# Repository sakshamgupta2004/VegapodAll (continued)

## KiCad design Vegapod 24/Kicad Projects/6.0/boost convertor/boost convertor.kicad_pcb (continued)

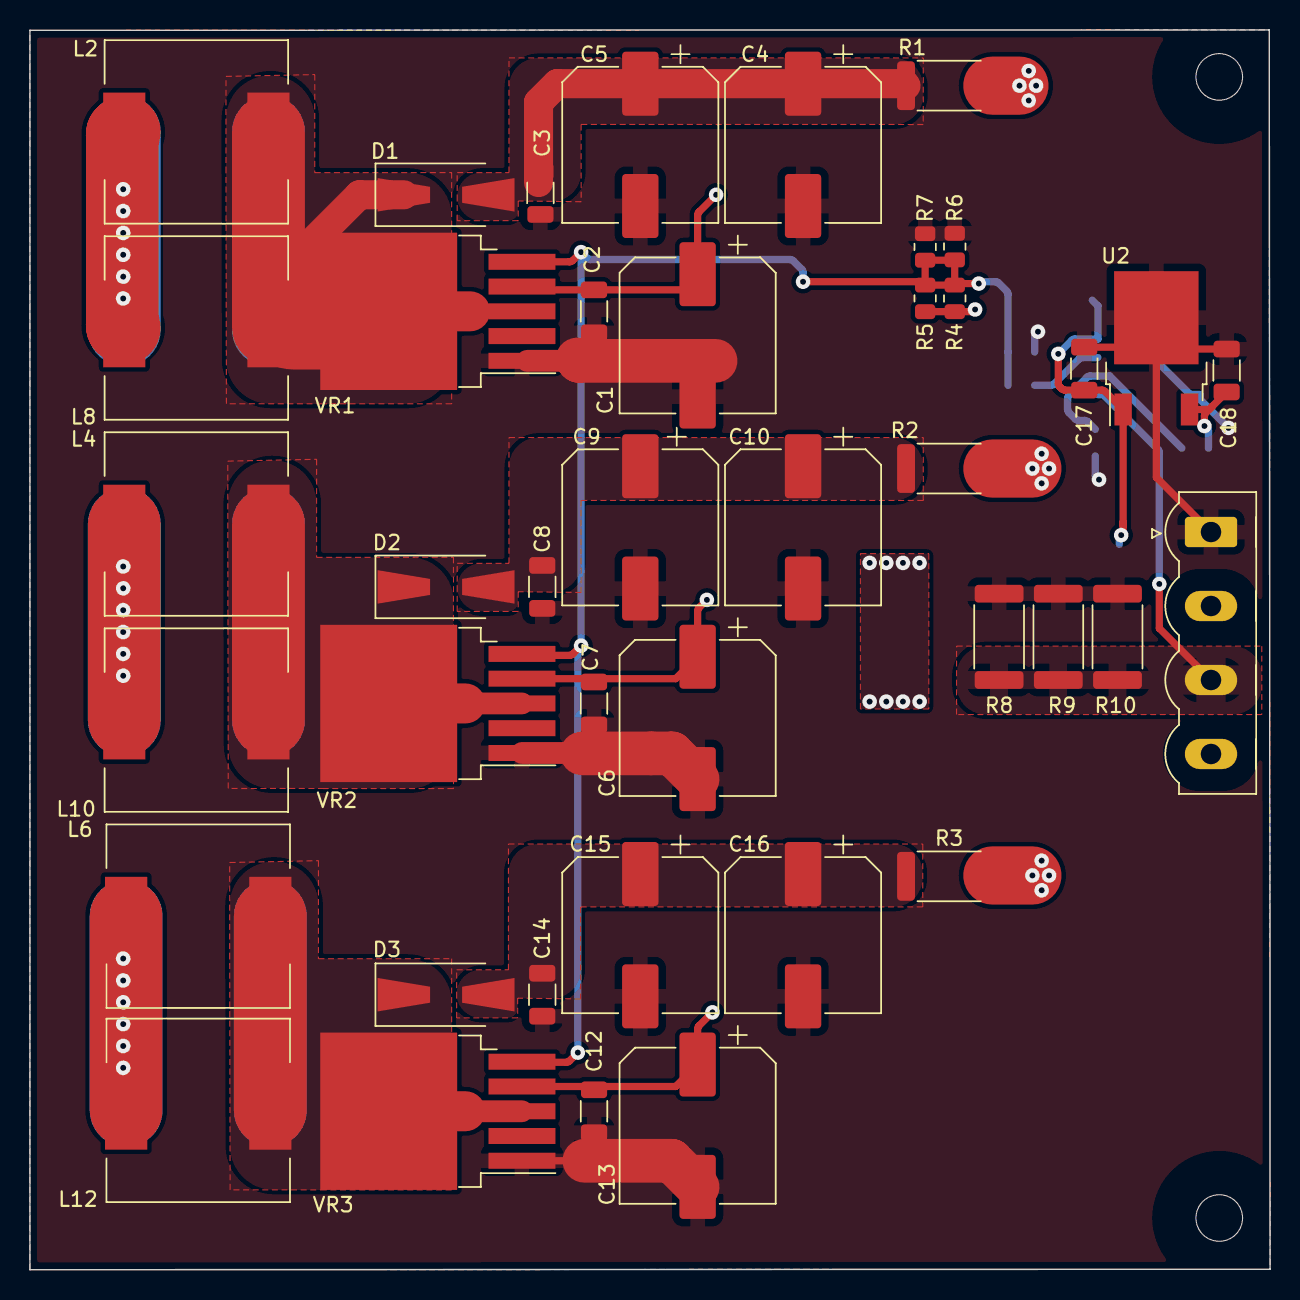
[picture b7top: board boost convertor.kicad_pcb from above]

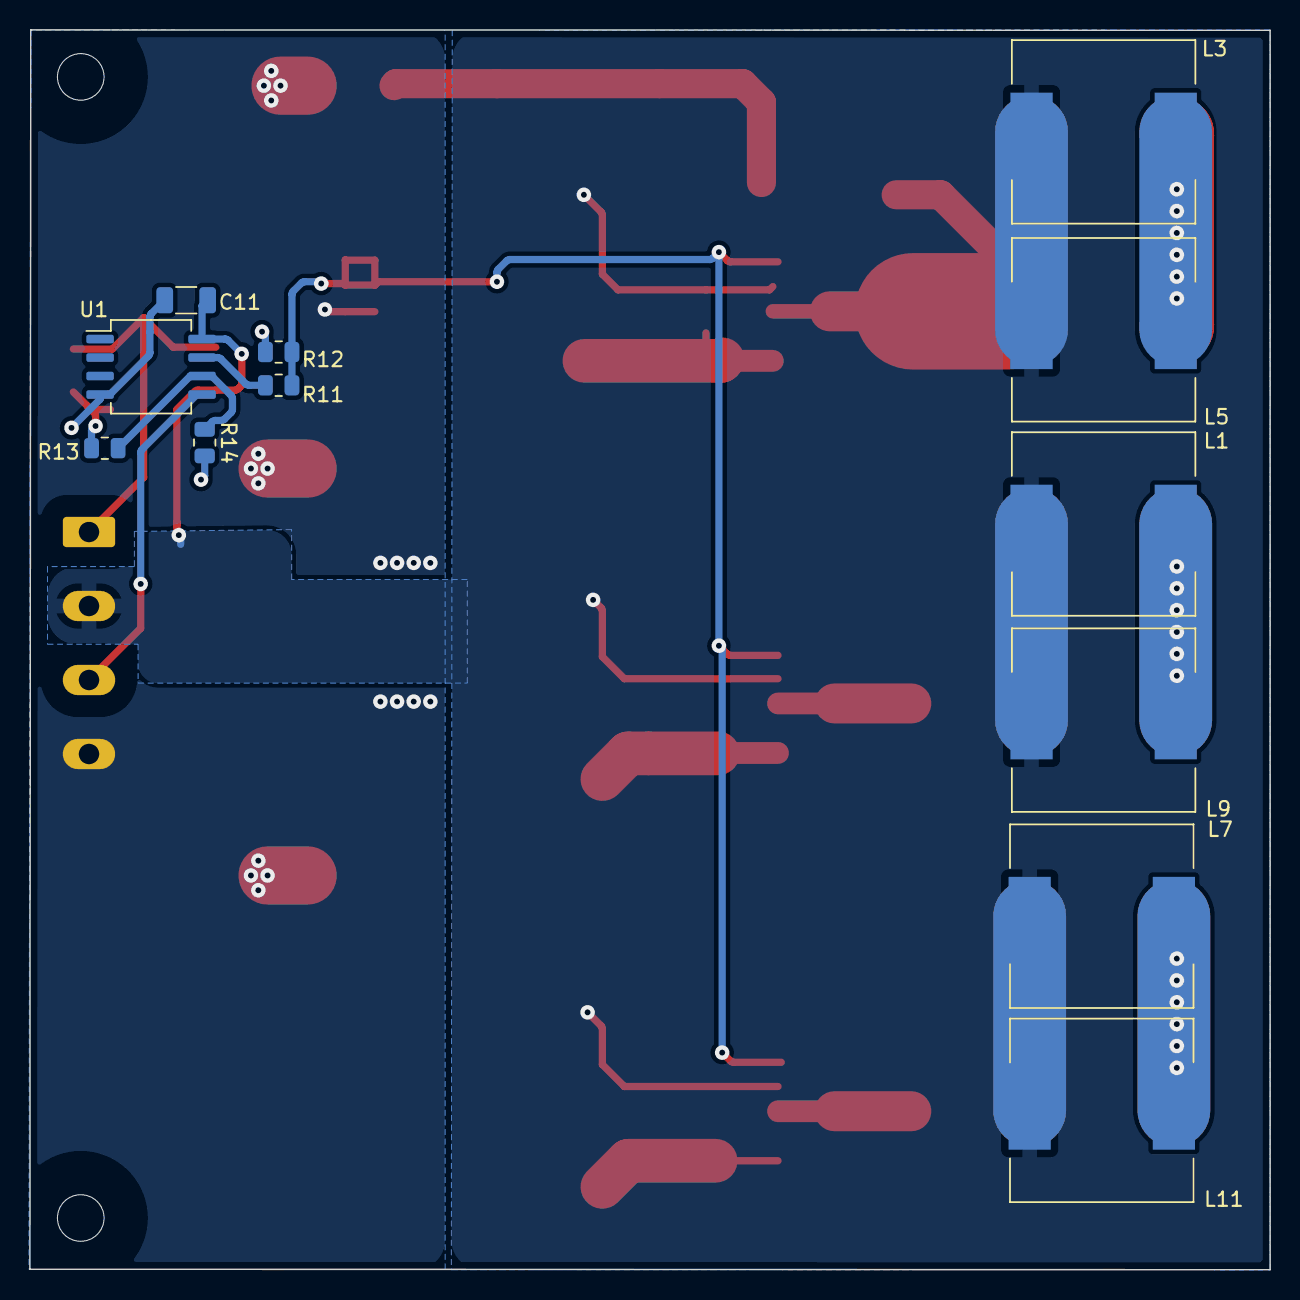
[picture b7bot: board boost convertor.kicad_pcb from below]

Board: 2 copper layers, 85.2 x 85.1 mm, 55 parts (12 on the bottom side), 17 nets.

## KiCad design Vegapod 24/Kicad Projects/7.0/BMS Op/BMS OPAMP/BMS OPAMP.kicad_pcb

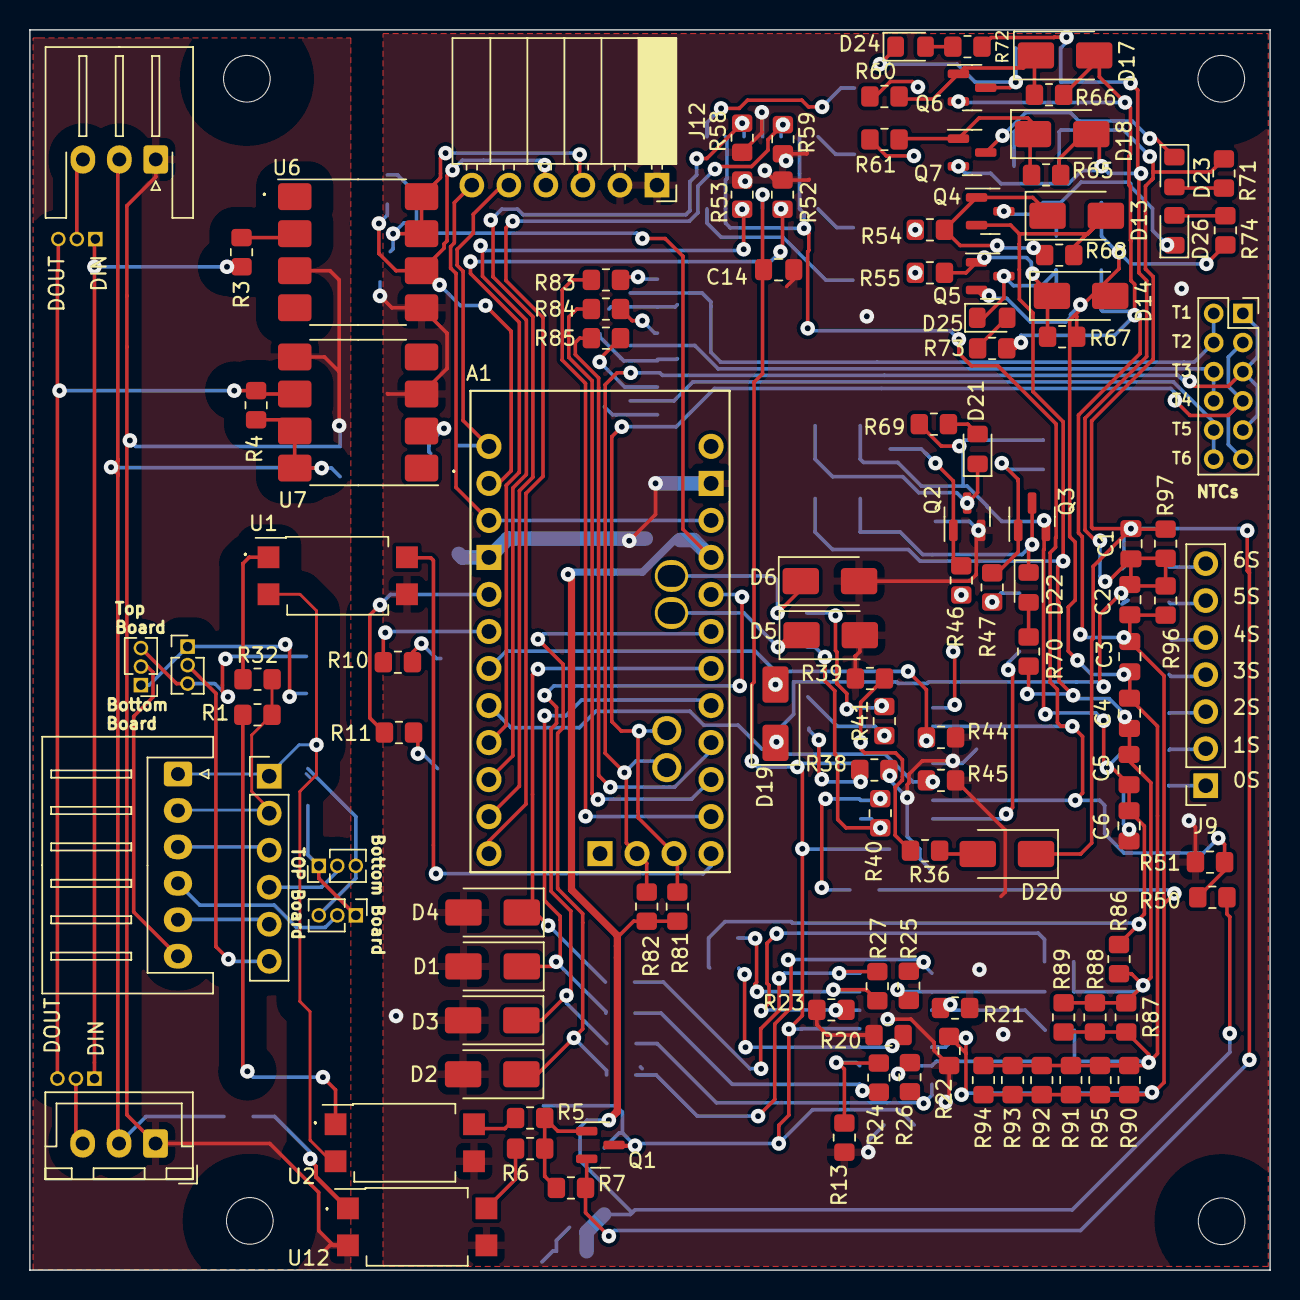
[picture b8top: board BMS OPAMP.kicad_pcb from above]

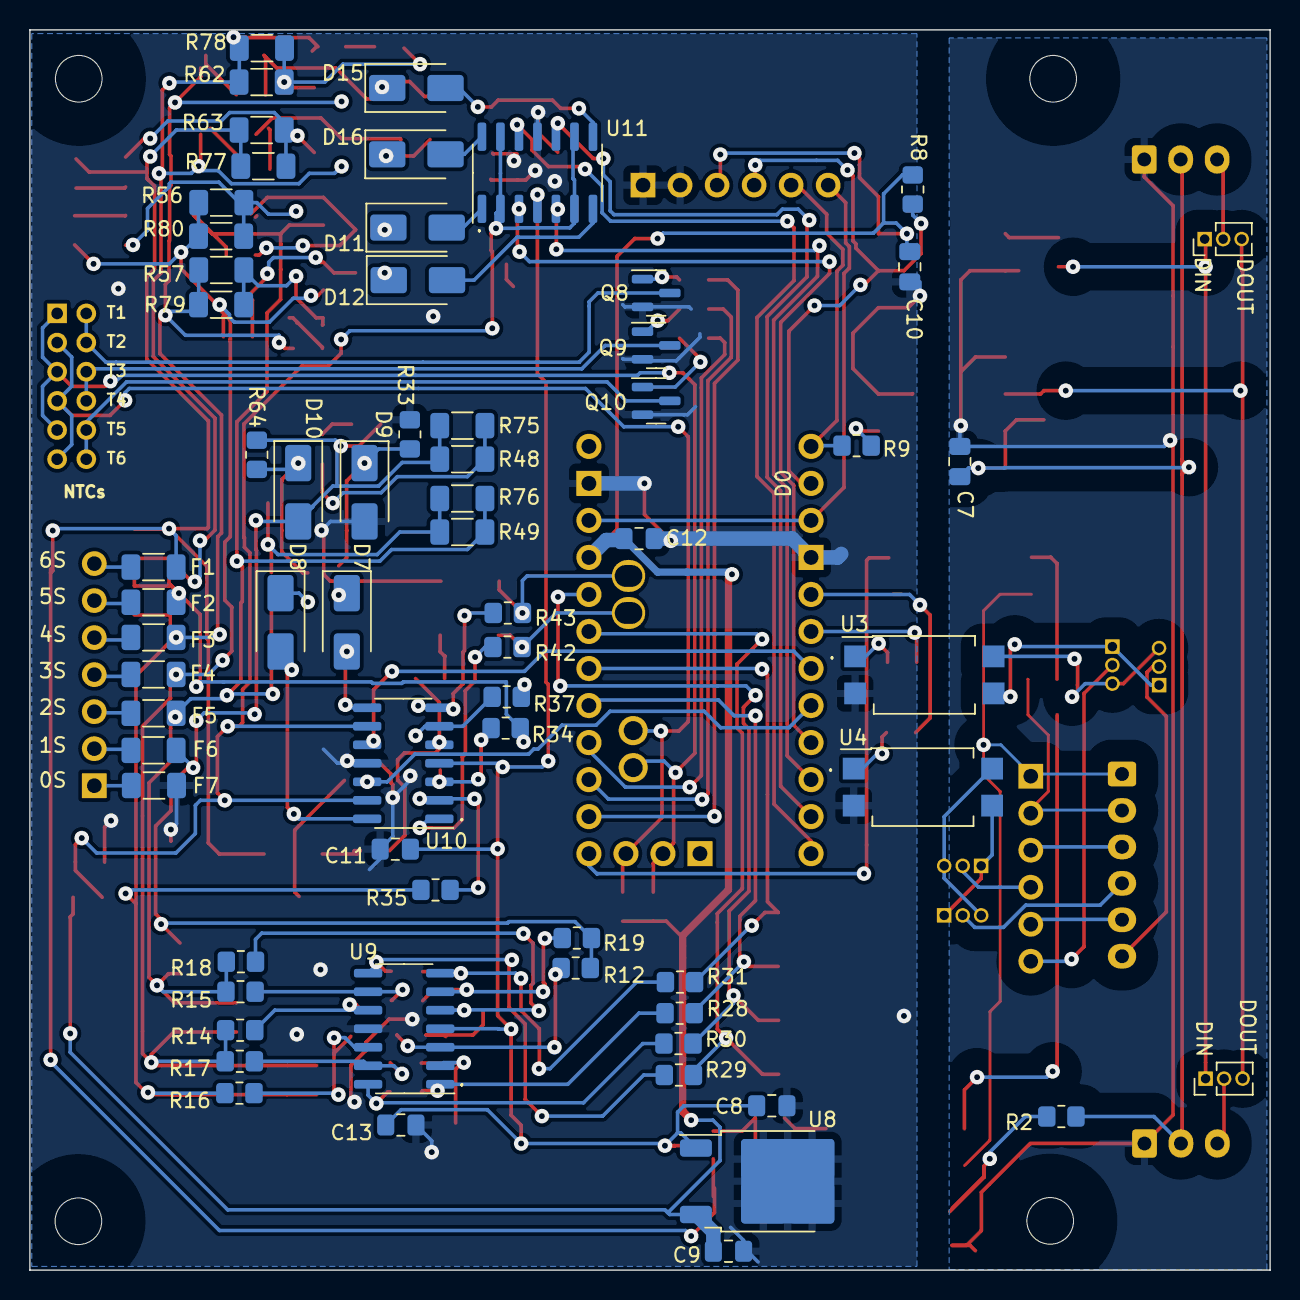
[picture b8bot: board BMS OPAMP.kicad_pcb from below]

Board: 2 copper layers, 85.1 x 85.1 mm, 183 parts (68 on the bottom side), 124 nets.

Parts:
A1: Clone_Pro_Mini_Socket_NoSPH
C1, C2, C3, C4, C5, C6, C7, C8, C9, C10, C11, C12, C13, C14: 1uF 25V; C_0805_2012Metric_Pad1.18x1.45mm_HandSolder
D1, D2, D3, D4, D5, D6: 5.1V Z; D_SMA
D7, D8, D11, D12, D15, D16: M7; D_SMA
D9, D10, D13, D14, D17, D18: 5V Z; D_SMA
D19, D20: Short It Out; D_SMA
D21, D22, D23, D24, D25, D26: LED; D_0805_2012Metric_Pad1.15x1.40mm_HandSolder
F1, F2, F3, F4, F5, F6, F7: Polyfuse_Small; R_1206_3216Metric_Pad1.30x1.75mm_HandSolder
H1, H2, H3, H4: MountingHole; MountingHole_3.2mm_M3
J1: CHG/DSCHG CTRL; JST_XH_S6B-XH-A_1x06_P2.50mm_Horizontal
J2: CHG/DSCHG CTRL CMP (SHORT DATA FOR STANDALONE); PinHeader_1x06_P2.54mm_Vertical
J3: Data IN/OUT; JST_XH_B3B-XH-A_1x03_P2.50mm_Vertical
J4: Data IN/OUT; JST_XH_S3B-XH-A-1_1x03_P2.50mm_Horizontal
J5, J6, J7, J8, J10, J11: Port Selector; PinHeader_1x03_P1.27mm_Vertical
J9: Balance Connector; PinSocket_1x07_P2.54mm_Vertical
J12: FTDI; PinSocket_1x06_P2.54mm_Horizontal
J18: Conn_02x06_Odd_Even; PinSocket_2x06_P2.00mm_Vertical
Q1: MMBT3906/FDN358P; SOT-23
Q2, Q3, Q4, Q5, Q6, Q7, Q8, Q9, Q10: MMBT3904/AM2304/AO3400; SOT-23
R1, R2, R3, R4, R8, R9, R10, R11, R28, R29, R30, R31, R32, R42, R43, R46, R47, R50, R51, R54, R55, R60, R69, R70, R71, R72, R73, R74, R83, R84, R85: 470; R_0805_2012Metric_Pad1.20x1.40mm_HandSolder
R5, R6, R7, R81, R82: 4.7k; R_0805_2012Metric_Pad1.20x1.40mm_HandSolder
R12, R14, R15, R16, R17, R18, R19, R21, R22, R23, R25, R26, R27, R33, R34, R35, R36, R37, R38, R39, R40, R41, R44, R45, R52, R53, R58, R59, R64, R65, R66, R67, R68, R86: 47K; R_0805_2012Metric_Pad1.20x1.40mm_HandSolder
R13, R20, R24, R87, R88, R89, R90, R91, R92, R93, R94, R95: 47k; R_0805_2012Metric_Pad1.20x1.40mm_HandSolder
R48, R49, R56, R57, R62, R63, R75, R76, R77, R78, R79, R80: 33; R_1206_3216Metric_Pad1.30x1.75mm_HandSolder
R61: SHORT OUT; R_0805_2012Metric_Pad1.20x1.40mm_HandSolder
R96: 4.7K; R_0805_2012Metric_Pad1.20x1.40mm_HandSolder
R97: 3.1k; R_0805_2012Metric_Pad1.20x1.40mm_HandSolder
U1, U2, U3, U4, U12: PC817; SSO-4_6.7x5.1mm_P2.54mm_Clearance8mm
U6, U7: 6N137; SOP-8_6.605x9.655mm_P2.54mm
U8: LM78M05_TO252; TO-252-2
U9, U10, U11: LM324; SOIC-14_3.9x8.7mm_P1.27mm

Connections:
5V: A1.Vcc1 (Vcc), C9.1, C10.1, C12.1, J12.3, R8.1, R50.2, R81.1, R82.1, U6.7 (EN), U6.8 (VCC), U8.3 (VO)
A0: A1.A0, D1.1 (K), R28.2
A1: A1.A1, D4.1 (K), R31.2
A2: A1.A2, D2.1 (K), R29.2
A3: A1.A3, D3.1 (K), R30.2
A4: A1.A4 (A4/SDA), D5.1 (K), R42.2
A5: A1.A5 (A5/SCL), D6.1 (K), R43.2
A6: A1.A6, J18.1, J18.5, J18.9, R82.2
A7: A1.A7, J18.3, J18.7, J18.11, R81.2
B0: A1.GND1 (GND), A1.GND2 (GND), C6.1, C8.2, C9.2, C10.2, C11.2, C12.2, C13.2, C14.2, D1.2 (A), D2.2 (A), D3.2 (A), D4.2 (A), D5.2 (A), D6.2 (A), D9.2 (A), F7.1, J12.1, J12.2, Q2.2 (E), Q8.2 (E), Q9.2 (E), Q10.2 (E), R13.1, R20.1, R21.1, R22.1, R23.1, R33.1, R38.1, R39.1, R44.2, R45.2, R51.1, R52.2, R53.2, R58.2, R59.2, U1.3, U2.3, U3.2, U4.2, U6.5 (GND), U7.3 (C), U8.2 (GND), U9.11 (V-), U10.11 (V-), U11.11 (V-), U12.3
B1: C5.1, C6.2, D10.2 (A), F6.1, Q3.2 (E), R12.1, R19.1, R48.1, R64.1, R69.1, R75.1, R86.1
B2: C4.1, C5.2, D13.2 (A), F5.1, Q4.2 (E), R15.1, R18.1, R49.1, R68.1, R70.1, R76.1, R86.2, R87.1, R88.1, R89.1
B3: C3.1, C4.2, D14.2 (A), F4.1, Q5.2 (E), R14.1, R17.1, R56.1, R67.1, R74.1, R80.1, R87.2, R88.2, R89.2, R90.1, R91.1, R92.1, R93.1, R94.1, R95.1
B4: C2.1, C3.2, D17.2 (A), F3.1, Q6.2 (E), R16.1, R35.1, R57.1, R66.1, R73.1, R79.1, R90.2, R91.2, R92.2, R93.2, R94.2, R95.2, R96.1
B5: C1.1, C2.2, D18.2 (A), D19.1 (K), F2.1, Q7.2 (E), R34.1, R62.1, R65.1, R72.1, R78.1, R96.2, R97.1
B6: C1.2, D20.1 (K), F1.1, Q1.2 (E), R7.2, R63.1, R71.1, R77.1, R97.2
CHARGEALLOW: A1.D2 (D2_INT0), R11.1
CHGDT+: J1.2, J2.2, R1.2, R32.2
CHGDT-: J1.1, J2.1, U1.2, U2.2
D0: A1.D4, R44.1, U10.10 (+)
D1: A1.D5, R45.1, U10.12 (+)
D2: A1.D6, R52.1, U11.3 (+)
D3: A1.D7, R53.1, U11.5 (+)
D4: A1.D8, R58.1, U11.10 (+)
D5: A1.D9, R59.1, U11.12 (+)
DCHG: A1.D10 (D10_CS), U1.4
DIN: J5.1, J6.1, R3.2
DIN_GND: C7.2, J3.1, J4.1, U6.3 (C), U7.5 (GND), U12.2
DIN_VCC: C7.1, J3.2, J4.2, R2.2, R4.1, U7.7 (EN), U7.8 (VCC)
DISCHARGEALLOW: A1.D3 (D3_INT1), R10.2
DOUT: J5.3, J6.3, R4.2, U7.6 (VO)
DRX: A1.D0 (D0/RX), J12.4, R8.2, U6.6 (VO)
DTEMP1: A1.D11 (D11_MOSI), R83.1
DTEMP2: A1.D12 (D12_MISO), R84.1
DTEMP3: A1.D13 (D13_SCK), R85.1
DTX: A1.D1 (D1/TX), J12.5, R9.2
NTC_GND1: J18.2, J18.4, Q8.3 (C)
NTC_GND2: J18.6, J18.8, Q9.3 (C)
NTC_GND3: J18.10, J18.12, Q10.3 (C)
unnamed: D7.2 (A), U10.8
unnamed: D7.1 (K), R46.1
unnamed: D8.2 (A), U10.14
unnamed: D8.1 (K), R47.1
unnamed: D9.1 (K), Q2.1 (B), R33.2, R46.2
unnamed: D10.1 (K), Q3.1 (B), R47.2, R64.2
unnamed: D11.2 (A), U11.1
unnamed: D11.1 (K), R54.1
unnamed: D12.2 (A), U11.7
unnamed: D12.1 (K), R55.1
unnamed: D13.1 (K), Q4.1 (B), R54.2, R68.2
unnamed: D14.1 (K), Q5.1 (B), R55.2, R67.2
unnamed: D15.2 (A), U11.8
unnamed: D15.1 (K), R60.1
unnamed: D16.2 (A), U11.14
unnamed: D16.1 (K), R61.1
unnamed: D17.1 (K), Q6.1 (B), R60.2, R66.2
unnamed: D18.1 (K), Q7.1 (B), R61.2, R65.2
unnamed: D19.2 (A), R37.1
unnamed: D20.2 (A), R36.1
unnamed: D21.2 (A), R69.2
unnamed: D21.1 (K), Q2.3 (C), R48.2, R75.2
unnamed: D22.2 (A), R70.2
unnamed: D22.1 (K), Q3.3 (C), R49.2, R76.2
unnamed: D23.2 (A), R71.2
unnamed: D23.1 (K), Q7.3 (C), R63.2, R77.2
unnamed: D24.2 (A), R72.2
unnamed: D24.1 (K), Q6.3 (C), R62.2, R78.2
unnamed: D25.2 (A), R73.2
unnamed: D25.1 (K), Q5.3 (C), R57.2, R79.2
unnamed: D26.2 (A), R74.2
unnamed: D26.1 (K), Q4.3 (C), R56.2, R80.2
unnamed: J1.3, J2.3
unnamed: J1.4, J10.2
unnamed: J1.5, J2.5
unnamed: J1.6, J7.2
unnamed: J2.6, J8.2
unnamed: J3.3, J6.2
unnamed: J4.3, J5.2
unnamed: J7.1, J8.1, U3.3
unnamed: J7.3, J8.3, U3.4
unnamed: F7.2, J9.1
unnamed: F6.2, J9.2
unnamed: F5.2, J9.3
unnamed: F4.2, J9.4
unnamed: F3.2, J9.5
unnamed: F2.2, J9.6
unnamed: F1.2, J9.7
unnamed: J10.1, J11.1, U4.3
unnamed: J10.3, J11.3, U4.4
unnamed: J2.4, J11.2
unnamed: Q1.1 (B), R5.2, R6.2, R7.1
unnamed: Q8.1 (B), R83.2
unnamed: Q9.1 (B), R84.2
unnamed: Q10.1 (B), R85.2
unnamed: R1.1, U2.1
unnamed: R2.1, U12.1
unnamed: R5.1, U2.4
unnamed: R6.1, U12.4
unnamed: R10.1, U3.1
unnamed: R11.2, U4.1
unnamed: R24.2, R28.1, U9.1
unnamed: R25.2, R29.1, U9.8
unnamed: R26.2, R30.1, U9.14
unnamed: R27.2, R31.1, U9.7
unnamed: R32.1, U1.1
unnamed: R40.2, R42.1, U10.1
unnamed: R41.2, R43.1, U10.7
unnamed: R3.1, U6.2 (A)
unnamed: R9.1, U7.2 (A)
unnamed: R12.2, R20.2, U9.3 (+)
unnamed: R13.2, R24.1, U9.2 (-)
unnamed: R18.2, R23.2, U9.5 (+)
unnamed: R19.2, R27.1, U9.6 (-)
unnamed: R14.2, R21.2, U9.10 (+)
unnamed: R15.2, R25.1, U9.9 (-)
unnamed: R16.2, R22.2, U9.12 (+)
unnamed: R17.2, R26.1, U9.13 (-)
unnamed: R34.2, R38.2, U10.3 (+)
unnamed: R35.2, R40.1, U10.2 (-)
unnamed: R36.2, R39.2, U10.5 (+)
unnamed: R37.2, R41.1, U10.6 (-)
POW: C8.1, C11.1, C13.1, C14.1, Q1.3 (C), U8.1 (VI), U9.4 (V+), U10.4 (V+), U11.4 (V+)
RST: A1.RST1 (RESET), A1.RST2 (RESET), J12.6
Vref: R50.1, R51.2, U10.9 (-), U10.13 (-), U11.2 (-), U11.6 (-), U11.9 (-), U11.13 (-)
